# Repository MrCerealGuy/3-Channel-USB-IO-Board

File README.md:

# 3-Channel-USB-IO-Board

## Steuern mit USB und AVR ATmega8 / 3-Kanal-Relais Karte

Bei diesem Projekt handelt es sich um ein 3-Kanal-Relais Board, das über USB gesteuert wird und in Cadsoft Eagle 7 Light entwickelt wurde. Für den USB-Anschluss wird der FTDI FT232RL USB/Seriell-Umsetzer IC genutzt, der die Kommunikation zwischen PC und dem Mikrocontroller ATmega8 übernimmt, für Windows/Linux gibt es entsprechende Treiber. An Port B des Mikrocontrollers sind drei Relais-Ausgänge angeschlossen, über die man kleinere Lasten wie Schrittmotoren usw. anschließen kann. Die Stromversorgung erfolgt komplett über die USB-Schnittstelle mit 5V/500mA.

Hinweis: Schaltplan/PCB-Layout wurden von mir nicht getestet, es handelt sich lediglich um einen frühen Prototyp.

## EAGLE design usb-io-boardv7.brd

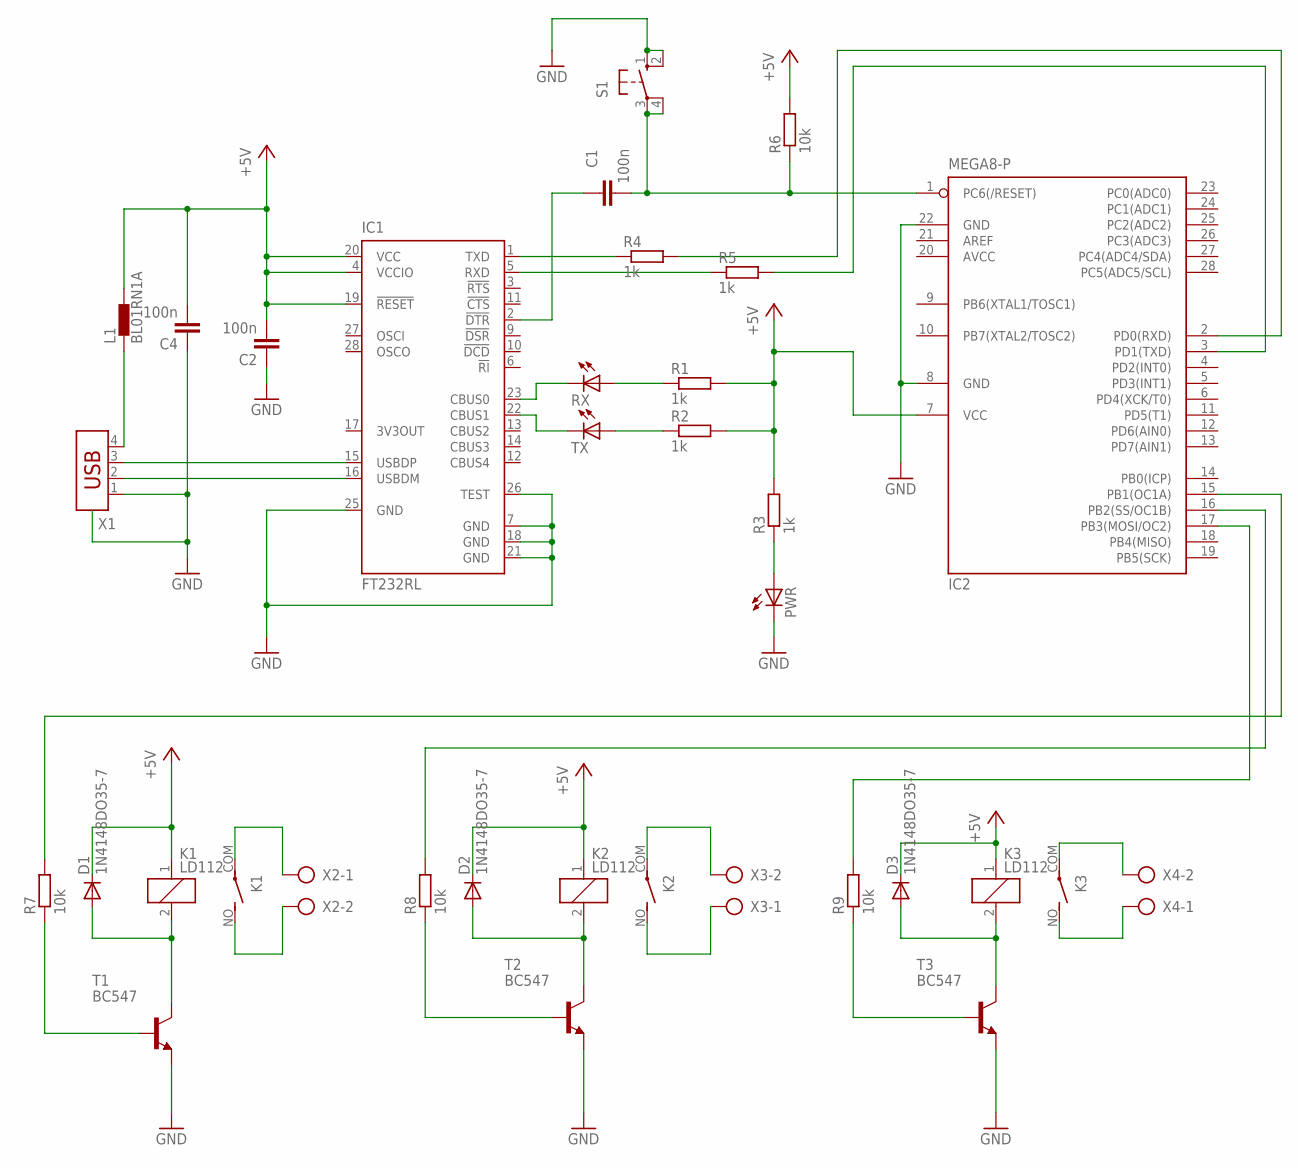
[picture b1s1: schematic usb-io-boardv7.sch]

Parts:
C1, C2, C4: 100n; C025-024X044
D1, D2, D3: 1N4148DO35-7; DO35-7
IC1: FT232RL; SSOP28
IC2: MEGA8-P; DIL28-3
K1, K2, K3: LD112; LD
L1: BL01RN1A
PWR: LED5MM
R1, R2, R3, R4, R5: 1k; 0204/5
R6, R7, R8, R9: 10k; 0204/5
RX: LED5MM
S1: 10-XX; B3F-10XX
T1, T2, T3: BC547; TO92
TX: LED5MM
X1: USB-787616; USB
X2, X3, X4: AK500/2

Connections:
+5V: C2.2, C4.2, D1.C, D2.C, D3.C, IC1.4 (VCCIO), IC1.19 (!RESET), IC1.20 (VCC), IC2.7 (VCC), K1.1, K2.1, K3.1, L1.2, R1.2, R2.2, R3.2, R6.2
AVCC: IC2.20 (AVCC)
GND: C2.1, C4.1, IC1.7 (GND), IC1.18 (GND), IC1.21 (GND), IC1.25 (GND), IC1.26 (TEST), IC2.8 (GND), IC2.22 (GND), PWR.K (C), S1.1 (S), S1.2 (S1), T1.1 (E), T2.1 (E), T3.1 (E), X1.1
unnamed: PWR.A, R3.1
unnamed: IC1.23 (CBUS0), RX.K (C)
unnamed: IC1.22 (CBUS1), TX.K (C)
unnamed: R1.1, RX.A
unnamed: R2.1, TX.A
unnamed: IC1.1 (TXD), R4.1
unnamed: IC1.5 (RXD), R5.1
unnamed: C1.1, IC1.2 (!DTR)
unnamed: C1.2, IC2.1 (PC6(/RESET)), R6.1, S1.3, S1.4 (P1)
unnamed: IC2.2 (PD0(RXD)), R4.2
unnamed: IC2.3 (PD1(TXD)), R5.2
unnamed: D1.A, K1.2, T1.3 (C)
unnamed: IC1.15 (USBDP), X1.3
unnamed: IC1.16 (USBDM), X1.2
unnamed: R7.1, T1.2 (B)
unnamed: IC2.15 (PB1(OC1A)), R7.2
unnamed: L1.1, X1.4
unnamed: K1.COM, X2.1
unnamed: K1.NO (S), X2.2
unnamed: IC2.17 (PB3(MOSI/OC2)), R9.2
unnamed: R8.1, T2.2 (B)
unnamed: D2.A, K2.2, T2.3 (C)
unnamed: IC2.16 (PB2(SS/OC1B)), R8.2
unnamed: R9.1, T3.2 (B)
unnamed: K2.COM, X3.2
unnamed: K2.NO (S), X3.1
unnamed: D3.A, K3.2, T3.3 (C)
unnamed: K3.COM, X4.2
unnamed: K3.NO (S), X4.1

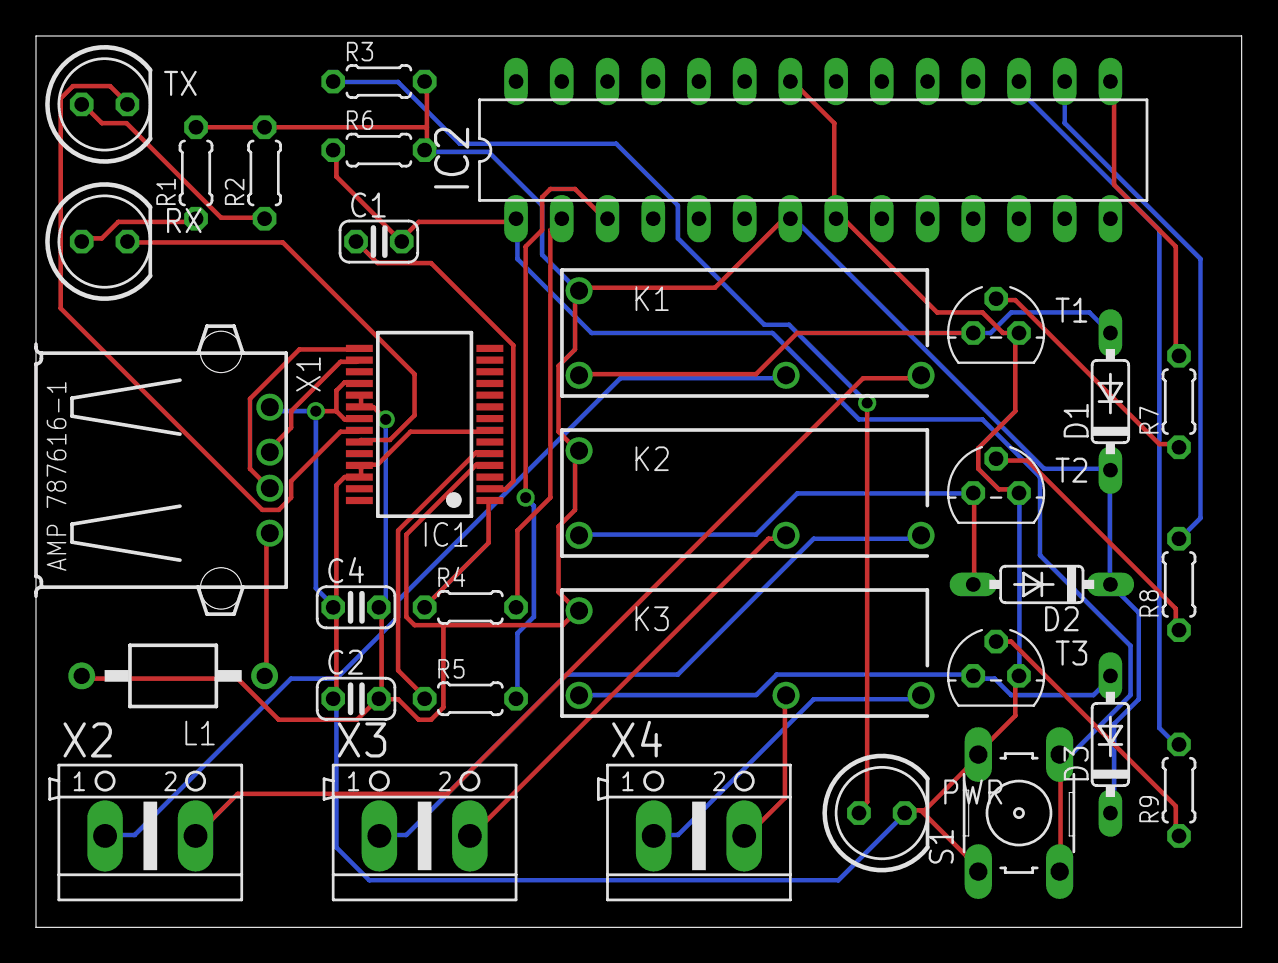
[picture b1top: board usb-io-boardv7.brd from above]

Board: 2 copper layers, 67.0 x 49.5 mm, 32 parts (0 on the bottom side), 31 nets.

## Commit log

2019-08-07 Initial upload
